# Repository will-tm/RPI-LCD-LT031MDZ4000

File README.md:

# RPI-LCD-LT031MDZ4000
Raspberry Pi panel driver for JDI LT031MDZ4000 720x720 display

# LCD Adapter board for Raspberry Pi

# Get kernel source
Refer to [rpi-source](https://github.com/RPi-Distro/rpi-source)

# Build & Install
```
git clone https://github.com/will-tm/RPI-LCD-LT031MDZ4000.git
cd RPI-LCD-LT031MDZ4000
make
make install
```
Then edit /boot/config.txt to add:
```
lcd_ignore=1
dtoverlay=vc4-kms-dsi-lt031mdz4000
```
and reboot

LCD pins defaults to:
- Reset - GPIO26
- BL_Enable - GPIO19
- PWM - GND

Default pins can be changed, for example:
```
#change Reset to GPIO5,BL_Enable to GPIO6
dtoverlay=vc4-kms-dsi-lt031mdz4000,bl-en=5,reset=6

```

# Hardware

Datasheet - [LT031MDZ4000-Datasheet](https://www.panoxdisplay.com/uploadfile/datasheet/LT031MDZ4000.pdf)

Proof-of-concept schematics - cf. repository KiCad project.

Important notes:
- This schematics comes with no warranties, use at your own risk

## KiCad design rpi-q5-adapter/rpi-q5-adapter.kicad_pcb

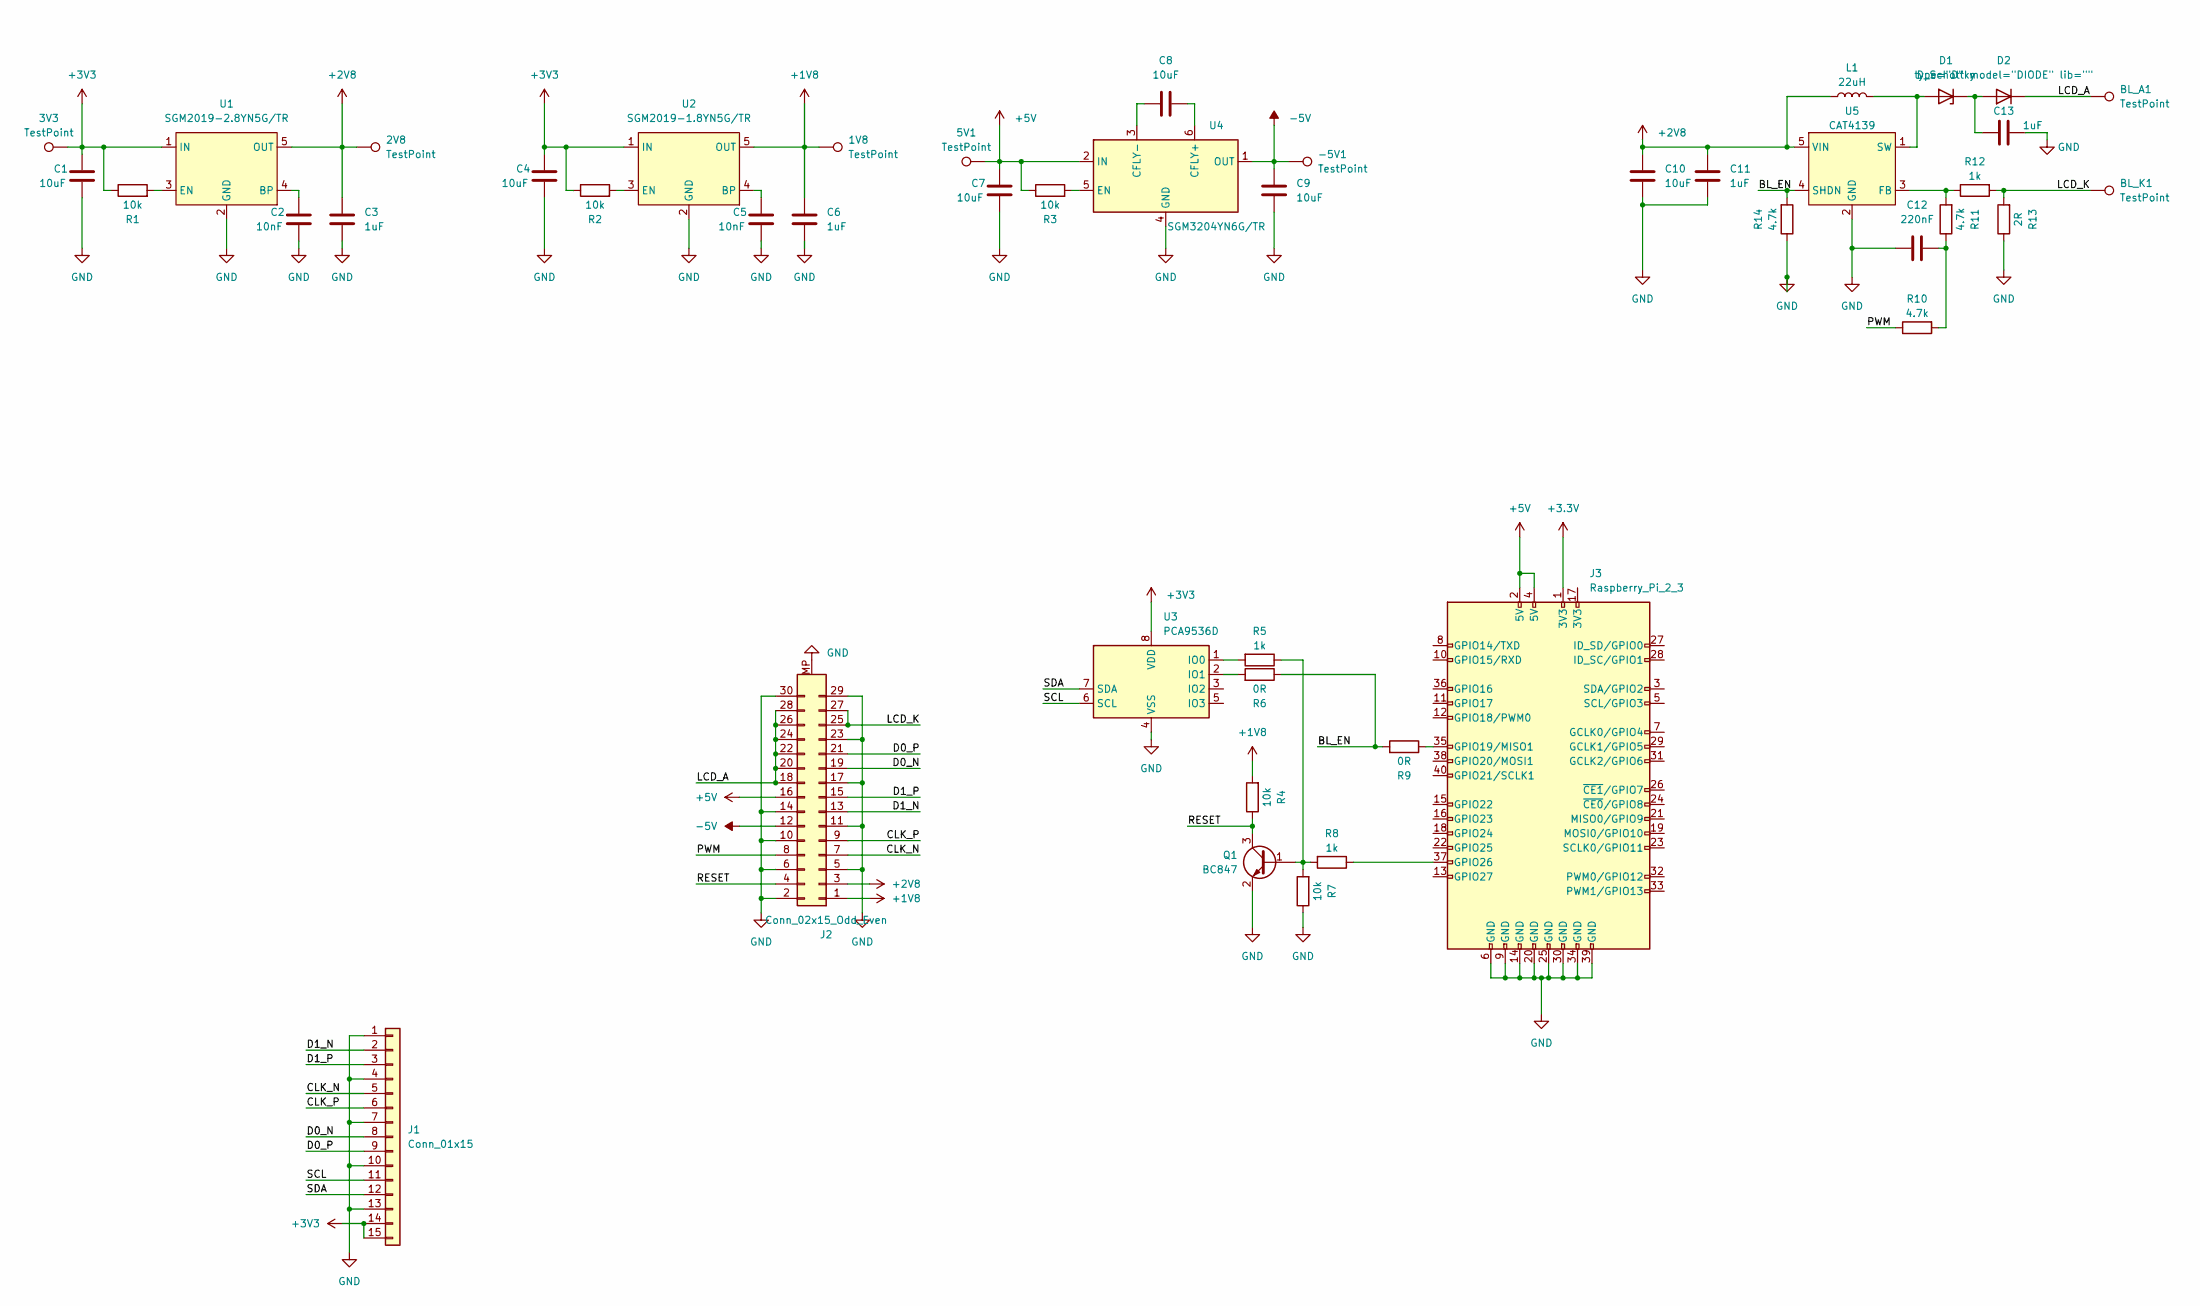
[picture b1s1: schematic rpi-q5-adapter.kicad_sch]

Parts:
1V8, 2V8, 3V3, 5V1: TestPoint; TestPoint_Pad_D1.0mm
-5V1: TestPoint; TestPoint_Pad_D1.0mm
BL_A1: TestPoint; TestPoint_Pad_D1.0mm
BL_K1: TestPoint; TestPoint_Pad_D1.0mm
C1, C4, C7, C8, C9, C10: 10uF; C_0805_2012Metric
C2, C5: 10nF; C_0603_1608Metric
C3, C6, C11, C13: 1uF; C_0603_1608Metric
C12: 220nF; C_0603_1608Metric
D1: D_Schottky; D_1206_3216Metric
D2: type="D" model="DIODE" lib=""; D_1206_3216Metric
J1: Conn_01x15; Molex_200528-0150_1x15-1MP_P1.00mm_Horizontal
J2: Conn_02x15_Odd_Even; BM14B(0.8)-30DS-0.4V(52)
J3: Raspberry_Pi_2_3; PinHeader_2x20_P2.54mm_Vertical
L1: 22uH; L_6.3x6.3_H3
Q1: BC847; SOT-23
R1, R2, R3, R4, R7: 10k; R_0603_1608Metric
R5, R8, R12: 1k; R_0603_1608Metric
R6, R9: 0R; R_0603_1608Metric
R10, R11, R14: 4.7k; R_0603_1608Metric
R13: 2R; R_0603_1608Metric
U1: SGM2019-2.8YN5G/TR; SOT-23-5_HandSoldering
U2: SGM2019-1.8YN5G/TR; SOT-23-5_HandSoldering
U3: PCA9536D; SOIC-8_3.9x4.9mm_P1.27mm
U4: SGM3204YN6G/TR; SOT-23-6_Handsoldering
U5: CAT4139; SOT-23-5_HandSoldering

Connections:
+1V8: 1V8.1, C6.1, J2.1, R4.2, U2.5 (OUT)
+2V8: 2V8.1, C3.1, C10.1, C11.1, J2.3, L1.1, U1.5 (OUT), U5.5 (VIN)
+5V: 5V1.1, C7.1, J2.16, J3.2 (5V), J3.4 (5V), R3.1, U4.2 (IN)
-5V: -5V1.1, C9.1, J2.12, U4.1 (OUT)
/BL_EN: R6.1, R9.2, R14.2, U5.4 (SHDN)
/CLK_N: J1.5, J2.7
/CLK_P: J1.6, J2.9
/D0_N: J1.8, J2.19
/D0_P: J1.9, J2.21
/D1_N: J1.2, J2.13
/D1_P: J1.3, J2.15
/LCD_A: BL_A1.1, D2.2 (K), J2.18, J2.20, J2.22, J2.24, J2.26, J2.28
/LCD_K: BL_K1.1, J2.25, J2.27, R12.2, R13.2
/PWM: J2.8, R10.1
/RESET: J2.4, Q1.3 (C), R4.1
/SCL: J1.11, U3.6 (SCL)
/SDA: J1.12, U3.7 (SDA)
GND: C1.2, C2.2, C3.2, C4.2, C5.2, C6.2, C7.2, C9.2, C10.2, C11.2, C12.2, C13.2, J1.1, J1.4, J1.7, J1.10, J1.13, J2.2, J2.5, J2.6, J2.10, J2.11, J2.14, J2.17, J2.23, J2.29, J2.30, J2.MP, J3.6 (GND), J3.9 (GND), J3.14 (GND), J3.20 (GND), J3.25 (GND), J3.30 (GND), J3.34 (GND), J3.39 (GND), Q1.2 (E), R7.1, R13.1, R14.1, U1.2 (GND), U2.2 (GND), U3.4 (VSS), U4.4 (GND), U5.2 (GND)
unnamed: C12.1, R10.2, R11.1
unnamed: D1.2 (A), L1.2, U5.1 (SW)
unnamed: C13.1, D1.1 (K), D2.1 (A)
unnamed: J3.35 (GPIO19/MISO1), R9.1
unnamed: J3.37 (GPIO26), R8.1
unnamed: Q1.1 (B), R5.1, R7.2, R8.2
unnamed: C2.1, U1.4 (BP)
unnamed: R1.2, U1.3 (EN)
unnamed: C5.1, U2.4 (BP)
unnamed: R2.2, U2.3 (EN)
unnamed: R5.2, U3.1 (IO0)
unnamed: R6.2, U3.2 (IO1)
unnamed: C8.2, U4.6 (CFLY+)
unnamed: C8.1, U4.3 (CFLY-)
unnamed: R3.2, U4.5 (EN)
unnamed: R11.2, R12.1, U5.3 (FB)

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
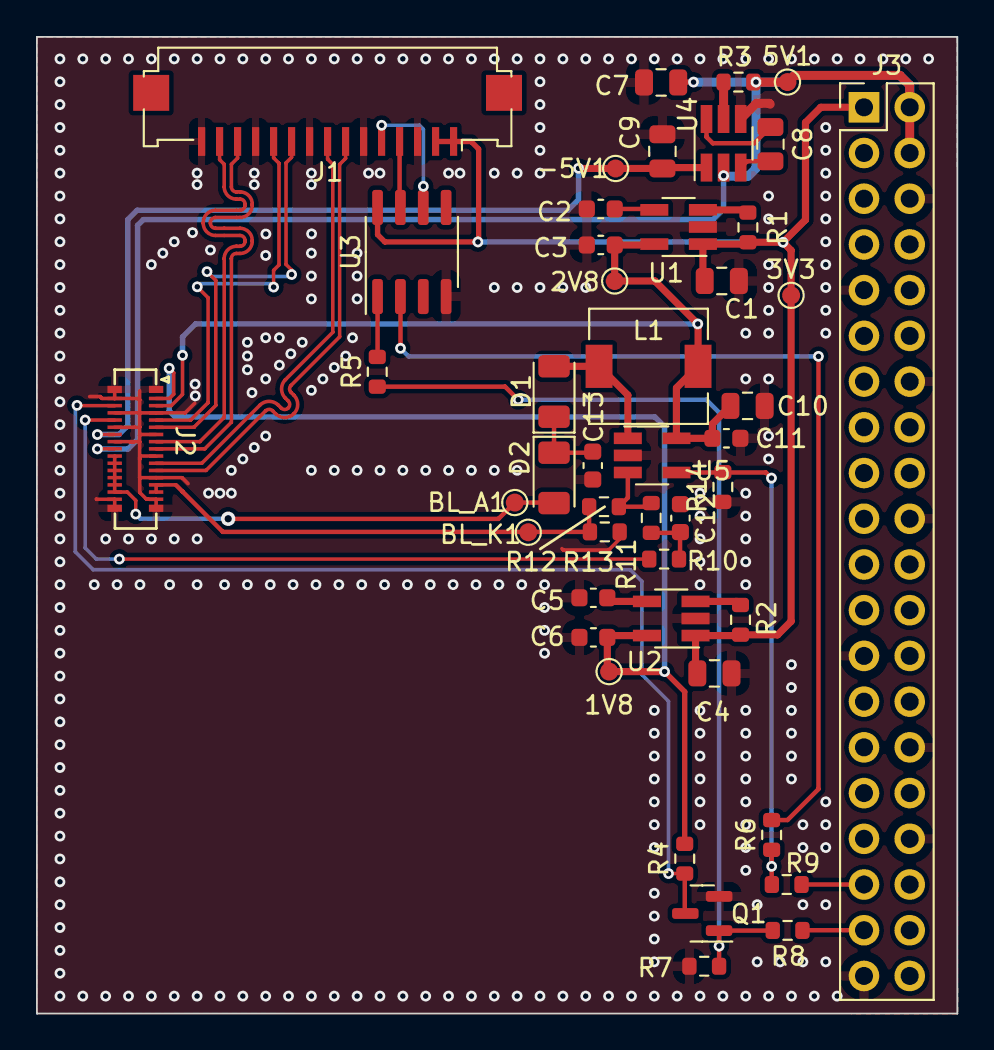
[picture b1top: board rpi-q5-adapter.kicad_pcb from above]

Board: 2 copper layers, 51.1 x 54.3 mm, 46 parts (0 on the bottom side), 35 nets.

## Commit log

2024-01-15 fix compilation on latest kernel
2024-01-15 added hardware board for evaluation
2024-01-15 mipi trace tuning
2024-01-15 better error management
2024-01-15 set prepare_upstream_first to allow mipi transfer at early stage
2024-01-16 clarify clock calculation
2024-01-19 prefer msleep to mdelay
2024-01-19 backlight additions
2024-01-22 added self credit
2024-01-23 fix vertical timings
2024-03-14 update for 6.6.y kernel
2025-12-06 typo fixes
